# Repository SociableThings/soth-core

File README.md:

# soth-core

---

## About
Hardware core module for Sociable Things Agent.

## Architecture

Agent

Core

## Data format
### GPS
```
{
    "year": 2015,
    "month": 4,
    "day": 12,
    "hour": 14,
    "minute": 0,
    "second": 48,
    "validity": 1,
    "latitude": 35.69020,
    "longitude": 139.69001,
    "speed": 0.74,
    "heading": 102.72
}
```

## Progress

Now prototyping

## GPS bore data

valid GPRMC

```
$GPGGA,150754.000,3540.6036,N,13940.9576,E,2,5,1.85,67.2,M,39.4,M,0000,0000*6A
$GPGLL,3540.6036,N,13940.9576,E,150754.000,A,D*5D
$GPGSA,A,3,28,03,01,06,17,,,,,,,,2.08,1.85,0.95*00
$GPGSV,4,1,13,03,71,081,15,28,56,235,35,17,49,320,16,01,42,051,15*77
$GPGSV,4,2,13,11,32,077,,32,27,046,,06,20,269,35,04,17,067,*76
$GPGSV,4,3,13,23,17,136,,09,05,164,,10,05,213,,44,04,260,*74
$GPGSV,4,4,13,19,03,118,*48
$GPRMC,150754.000,A,3540.6036,N,13940.9576,E,0.06,198.48,110415,,,D*60
$GPVTG,198.48,T,,M,0.06,N,0.12,K,D*31
```

invalid GPRMC

```
$GPRMC,142307.497,V,,,,,0.00,0.00,110415,,,N*44
```

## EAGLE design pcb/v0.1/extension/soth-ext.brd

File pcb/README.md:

# soth-core PCB

---

## BOM list

| Parts # |   Parts Name   | Manufacture Parts # | Footprint | Pin | Manufacture | Source | Document |
|--------:|---------------:|--------------------:|----------:|----:|------------:|-------:|---------:|
|       U1|             MCU|      ATXMEGA32D4-AUR|       TQFP|   44|       Atmel |[Akizuki](http://akizukidenshi.com/catalog/g/gI-06993/)|[AVR XMEGA D Manual](http://www.atmel.com/ja/jp/Images/Atmel-8210-8-and-16-bit-AVR-Microcontrollers-XMEGA-D_Manual.pdf), [ATxmega32D4 Complete](http://www.atmel.com/ja/jp/Images/Atmel-8135-8-and-16-bit-AVR-microcontroller-ATxmega16D4-32D4-64D4-128D4_datasheet.pdf)|
|      IC1|USB Serial Conv.|    AE-FT231X(FT231X)|DIP(500MIL)|   18|      Akizuki|[Akizuki](http://akizukidenshi.com/catalog/g/gK-06894/)|[Manual](http://akizukidenshi.com/download/ds/akizuki/ae_ft231x_manual.pdf)|
|    IC3,4|  3-State Buffer|            TC7SZ125F|       SSOP|    5|      Toshiba|[Akizuki](http://akizukidenshi.com/catalog/g/gI-06481/)|[Datasheet](http://toshiba.semicon-storage.com/info/docget.jsp?did=20048&prodName=TC7SZ125FU)|
|      IC5| Pressure Sensor|      12113(LPS331AP)|        DIP|   10|Strawberry Linux|[Strawberry Linux](https://strawberry-linux.com/catalog/items?code=12113)|[Manual](https://strawberry-linux.com/pub/lps331ap-manual.pdf)|

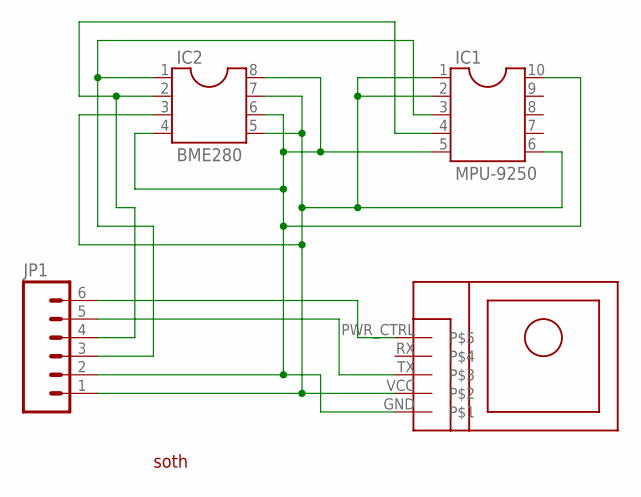
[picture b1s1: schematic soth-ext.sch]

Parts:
IC1: MPU-9250; DIL10
IC2: BME280; DIL08
JP1: M06SILK_FEMALE_PTH; 1X06
U$1: GM318B
U$2: SOTH_LOGO; SILK_LOGO

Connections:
GND: IC1.5, IC1.10, IC2.4, IC2.6, IC2.8, JP1.2, U$1.GND
unnamed: IC1.1, IC1.2, IC1.6, IC2.3, IC2.5, IC2.7, JP1.1, U$1.VCC
unnamed: JP1.5, U$1.TX
unnamed: JP1.6, U$1.PWR_CTRL
unnamed: IC1.4, IC2.2, JP1.4
unnamed: IC1.3, IC2.1, JP1.3

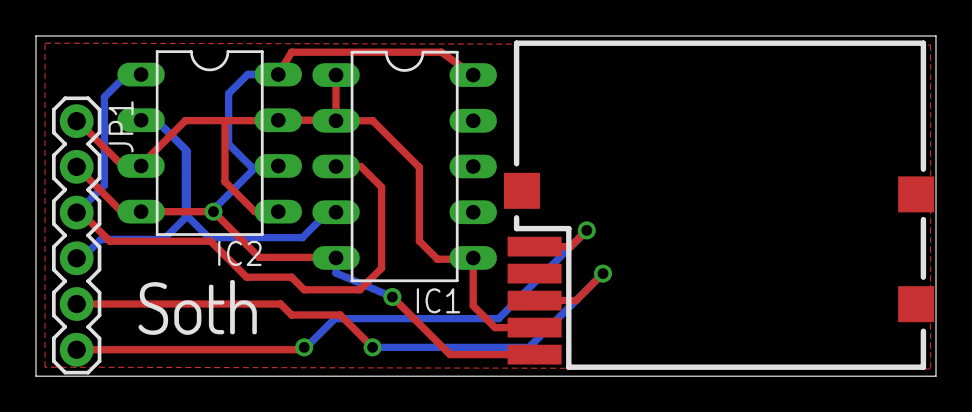
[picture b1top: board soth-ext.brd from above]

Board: 2 copper layers, 50.0 x 18.9 mm, 5 parts (0 on the bottom side), 6 nets.

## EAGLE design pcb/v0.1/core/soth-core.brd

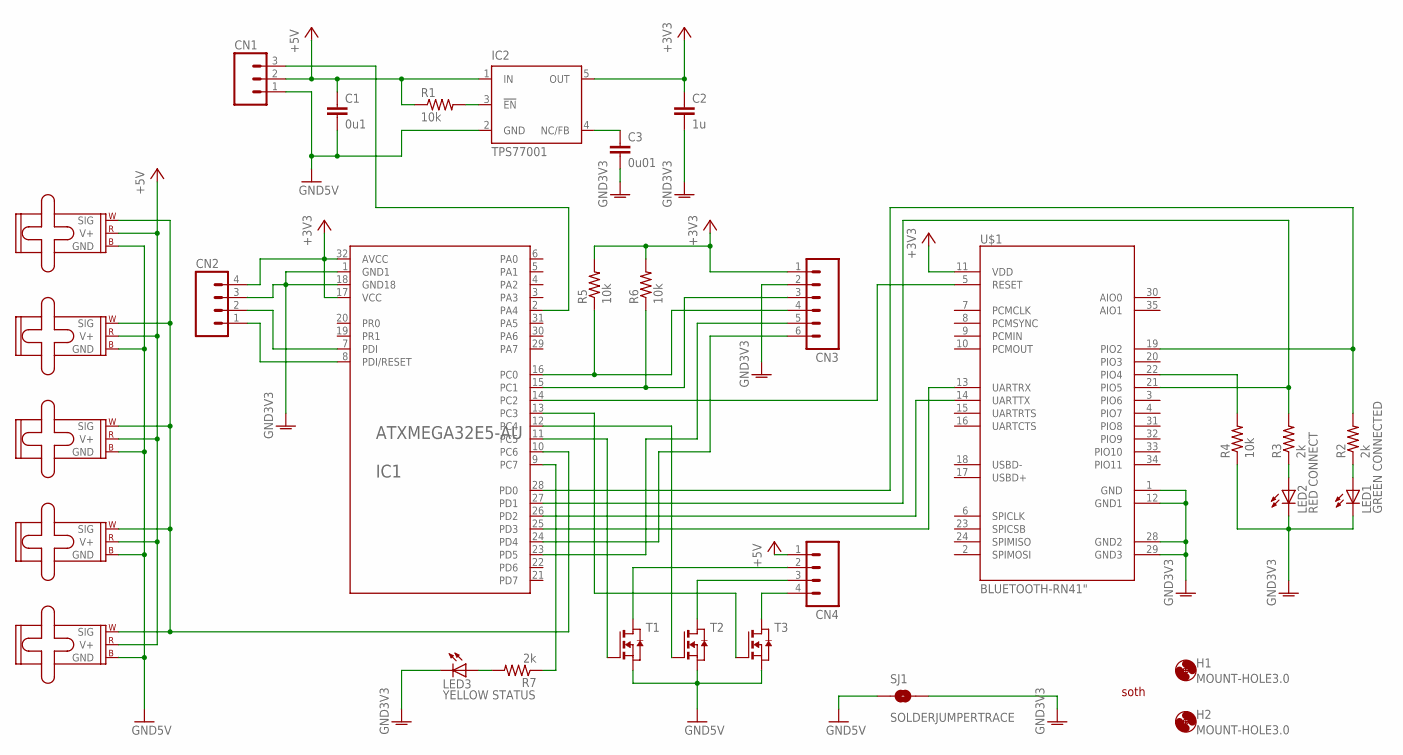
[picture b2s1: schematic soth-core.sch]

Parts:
C1: 0u1; C1608
C2: 1u; C1608
C3: 0u01; C1608
CN1: M03PTH; 1X03
CN2, CN4: M04PTH; 1X04
CN3: M06SILK_FEMALE_PTH; 1X06
H1, H2: MOUNT-HOLE3.0; 3,0
IC1: ATXMEGA32E5-AU; TQFP32-08
IC2: TPS77001; SOT23-DBV
LED1: GREEN CONNECTED; CHIPLED_1206
LED2: RED CONNECT; CHIPLED_1206
LED3: YELLOW STATUS; CHIPLED_1206
M1, M2, M3, M4, M5: SMALL_SERVO; 1X03
R1, R4, R5, R6: 10k; R0603
R2, R3, R7: 2k; R0603
SJ1: SOLDERJUMPERTRACE; SJ_2S-TRACE
T1, T2, T3: NMOSSOT23; SOT-23
U$1: BLUETOOTH-RN41"; RN41
U$2: SOTH_LOGO; SILK_LOGO

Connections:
+3V3: C2.1, CN2.4, CN3.1, IC1.17 (VCC), IC1.32 (AVCC), IC2.5 (OUT), R5.2, R6.2, U$1.11 (VDD)
+5V: C1.1, CN1.2, CN4.1, IC2.1 (IN), M1.2 (V+), M2.2 (V+), M3.2 (V+), M4.2 (V+), M5.2 (V+), R1.1
GND: C1.2, CN1.1, IC2.2 (GND), M1.3 (GND), M2.3 (GND), M3.3 (GND), M4.3 (GND), M5.3 (GND), SJ1.1, T1.2 (S), T2.2 (S), T3.2 (S)
GNDA: C2.2, C3.2, CN2.3, CN3.2, IC1.1 (GND1), IC1.18 (GND18), LED1.C, LED2.C, LED3.C, R4.1, SJ1.2, U$1.1 (GND), U$1.12 (GND1), U$1.28 (GND2), U$1.29 (GND3)
unnamed: CN4.2, T1.1 (D)
unnamed: IC2.3 (!EN), R1.2
unnamed: IC1.26 (PD2), U$1.14 (UARTTX)
unnamed: CN2.2, IC1.7 (PDI)
unnamed: CN2.1, IC1.8 (PDI/RESET)
unnamed: IC1.25 (PD3), U$1.13 (UARTRX)
unnamed: IC1.27 (PD1), R3.2, U$1.21 (PIO5)
unnamed: LED2.A, R3.1
unnamed: LED1.A, R2.1
unnamed: IC1.28 (PD0), R2.2, U$1.19 (PIO2)
unnamed: R4.2, U$1.22 (PIO4)
unnamed: CN3.4, IC1.16 (PC0), R5.1
unnamed: CN3.3, IC1.15 (PC1), R6.1
unnamed: CN1.3, IC1.2 (PA4)
unnamed: CN4.3, T2.1 (D)
unnamed: CN4.4, T3.1 (D)
unnamed: IC1.9 (PC7), R7.1
unnamed: IC1.11 (PC5), T1.3 (G)
unnamed: CN3.6, IC1.24 (PD4)
unnamed: IC1.10 (PC6), M1.1 (SIG), M2.1 (SIG), M3.1 (SIG), M4.1 (SIG), M5.1 (SIG)
unnamed: CN3.5, IC1.23 (PD5)
unnamed: IC1.12 (PC4), T2.3 (G)
unnamed: IC1.13 (PC3), T3.3 (G)
unnamed: LED3.A, R7.2
unnamed: C3.1, IC2.4 (NC/FB)
unnamed: IC1.14 (PC2), U$1.5 (RESET)

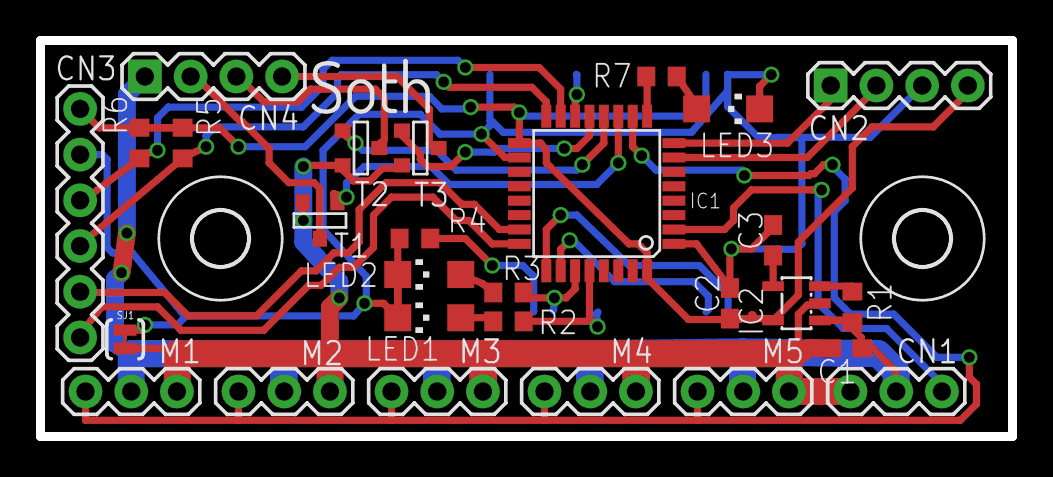
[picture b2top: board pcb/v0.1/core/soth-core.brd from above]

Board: 2 copper layers, 54.0 x 22.0 mm, 32 parts (1 on the bottom side), 30 nets.

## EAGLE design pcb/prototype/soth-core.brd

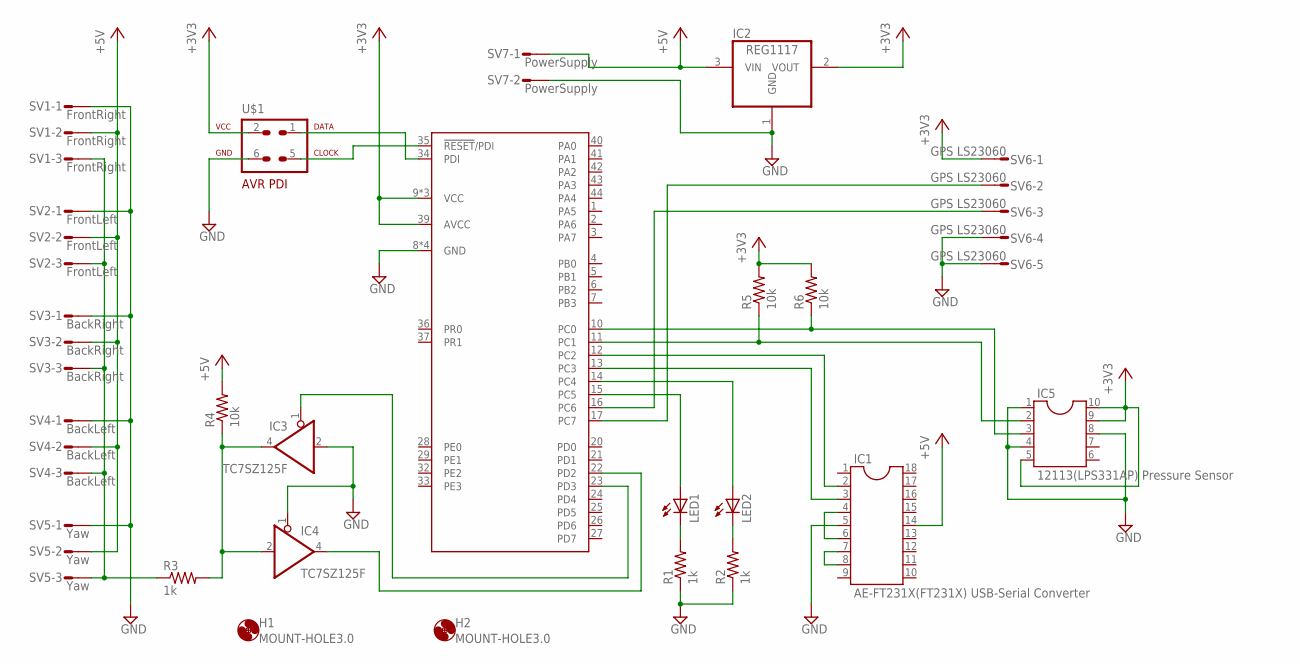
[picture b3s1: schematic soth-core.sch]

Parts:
H1, H2: MOUNT-HOLE3.0; 3,0
IC1: AE-FT231X(FT231X) USB-Serial Converter; SOCKET-18
IC2: REG1117; SOT223
IC3, IC4: TC7SZ125F; SOT23-5
IC5: 12113(LPS331AP) Pressure Sensor; DIL10
LED1, LED2: LED; SMARTLED-TTW
R1, R2, R3: 1k; R0805
R4, R5, R6: 10k; R0805
SV1: FrontRight; S03P
SV2: FrontLeft; S03P
SV3: BackRight; S03P
SV4: BackLeft; S03P
SV5: Yaw; S03P
SV6: GPS LS23060; S05P
SV7: PowerSupply; S02P
U1: ATXMEGA32D4-AU; TQFP-44A-44
U$1: AVR-PDIVERT; AVR-ISP-6

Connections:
+3V3: IC2.2 (VOUT), IC5.5, IC5.9, IC5.10, R5.2, R6.2, SV6.1, U1.9 (VCC), U1.19 (VCC), U1.31 (VCC), U1.39 (AVCC), U$1.2
+5V: IC1.14, IC2.3 (VIN), R4.2, SV1.2, SV2.2, SV3.2, SV4.2, SV5.2, SV7.1
GND: IC1.5, IC2.1 (GND), IC3.2 (I), IC3.3 (GND), IC4.1 (OE), IC4.3 (GND), IC5.1, IC5.4, IC5.8, R1.1, R2.1, SV1.1, SV2.1, SV3.1, SV4.1, SV5.1, SV6.4, SV6.5, SV7.2, U1.8 (GND), U1.18 (GND), U1.30 (GND), U1.38 (GND), U$1.6
unnamed: R3.1, SV1.3, SV2.3, SV3.3, SV4.3, SV5.3
unnamed: LED1.A@1 (A), U1.15 (PC5)
unnamed: LED2.A@1 (A), U1.14 (PC4)
unnamed: LED1.C@1 (C), R1.2
unnamed: U1.35 (!RESET!/PDI), U$1.5
unnamed: U1.34 (PDI), U$1.1
unnamed: LED2.C@1 (C), R2.2
unnamed: IC4.4 (O), U1.22 (PD2)
unnamed: SV6.2, U1.17 (PC7)
unnamed: IC1.2, U1.12 (PC2)
unnamed: IC1.3, U1.13 (PC3)
unnamed: IC1.7, IC1.8
unnamed: IC1.4, IC1.6
unnamed: SV6.3, U1.16 (PC6)
unnamed: IC3.1 (OE), U1.23 (PD3)
unnamed: IC3.4 (O), IC4.2 (I), R3.2, R4.1
unnamed: IC5.3, R6.1, U1.10 (PC0)
unnamed: IC5.2, R5.1, U1.11 (PC1)
VCC: IC3.5 (VCC), IC4.5 (VCC)

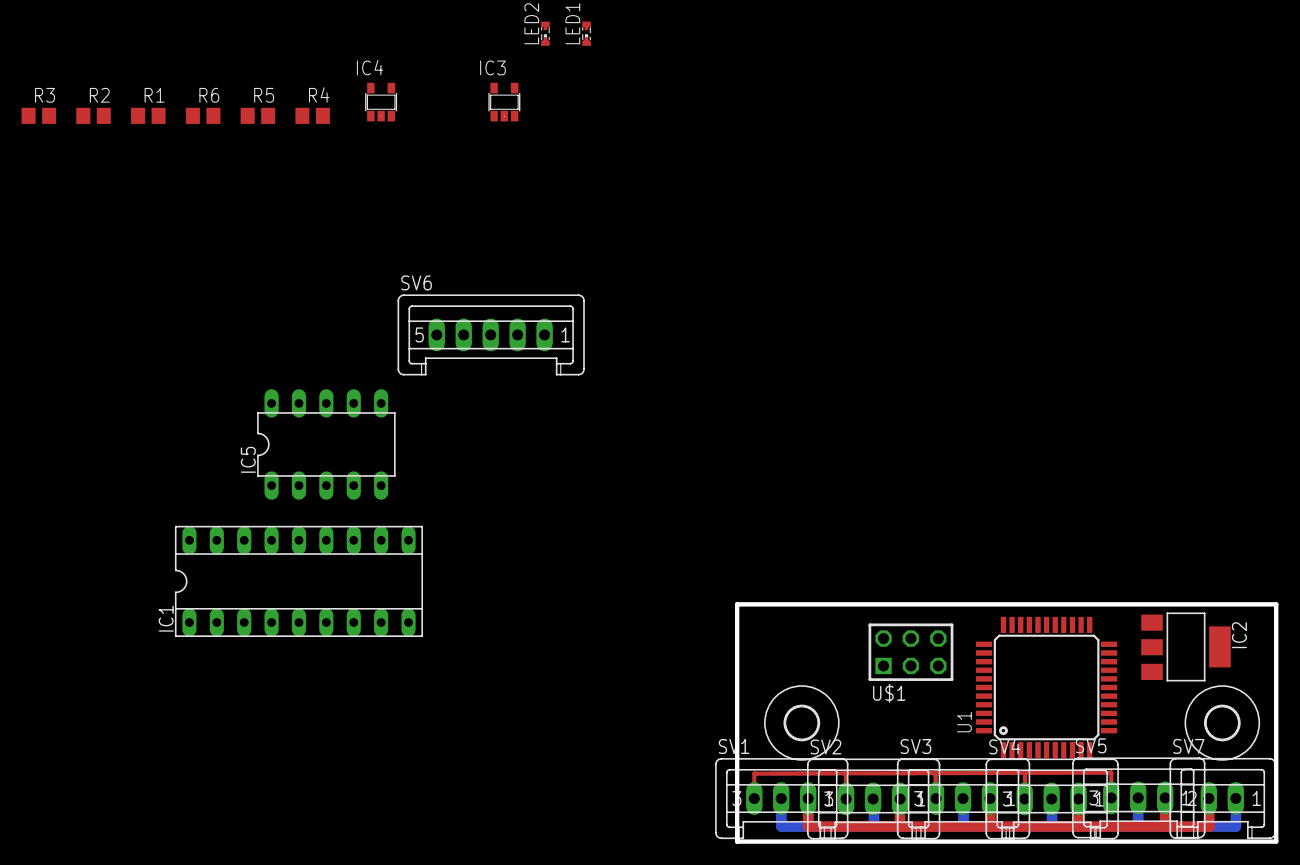
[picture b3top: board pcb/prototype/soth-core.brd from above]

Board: 2 copper layers, 50.0 x 22.0 mm, 24 parts (0 on the bottom side), 22 nets.

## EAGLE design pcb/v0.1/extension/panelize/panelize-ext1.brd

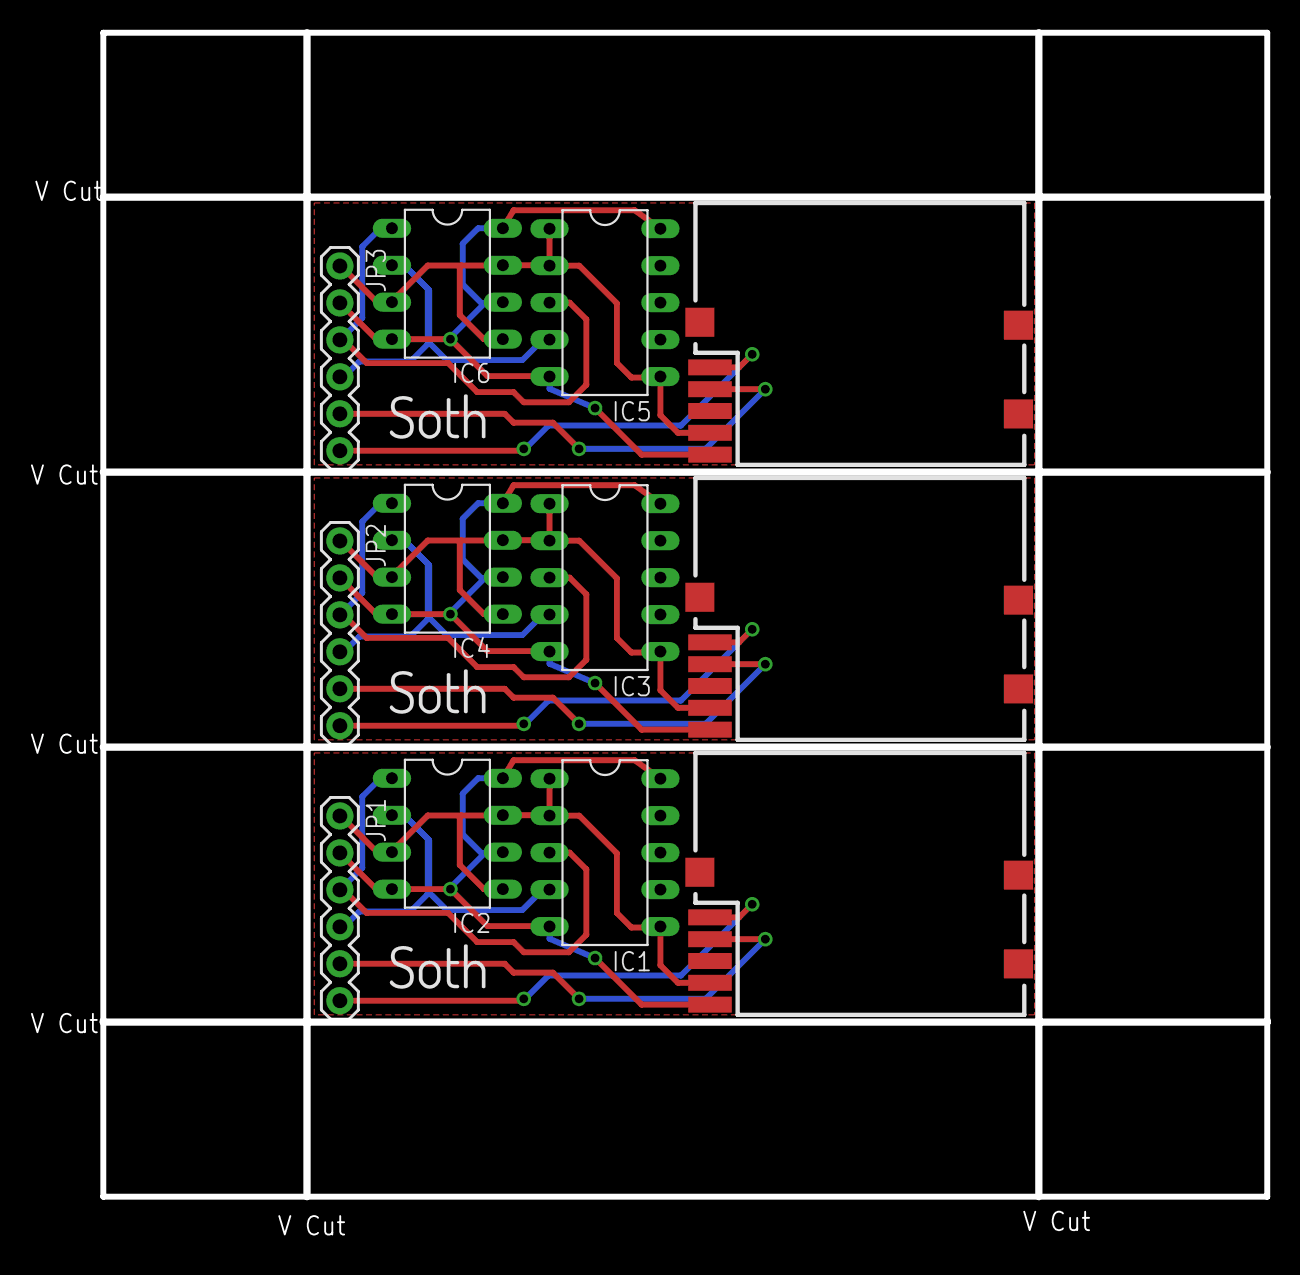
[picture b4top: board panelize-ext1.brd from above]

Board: 2 copper layers, 80.0 x 80.0 mm, 15 parts (0 on the bottom side), 18 nets.

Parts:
IC1, IC3, IC5: MPU-9250; DIL10
IC2, IC4, IC6: BME280; DIL08
JP1, JP2, JP3: 1X06
U$1, U$3, U$5: GM318B
U$2, U$4, U$6: SOTH_LOGO; SILK_LOGO

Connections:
GND: IC1.5, IC1.10, IC2.4, IC2.6, IC2.8, JP1.2, U$1.GND
GND1: IC3.5, IC3.10, IC4.4, IC4.6, IC4.8, JP2.2, U$3.GND
GND2: IC5.5, IC5.10, IC6.4, IC6.6, IC6.8, JP3.2, U$5.GND
unnamed: JP2.5, U$3.RX
unnamed: IC1.1, IC1.2, IC1.6, IC2.3, IC2.5, IC2.7, JP1.1, U$1.VCC
unnamed: JP1.5, U$1.RX
unnamed: JP1.6, U$1.PWR_CTRL
unnamed: JP2.6, U$3.PWR_CTRL
unnamed: IC3.4, IC4.2, JP2.4
unnamed: IC1.4, IC2.2, JP1.4
unnamed: IC1.3, IC2.1, JP1.3
unnamed: IC3.3, IC4.1, JP2.3
unnamed: IC3.1, IC3.2, IC3.6, IC4.3, IC4.5, IC4.7, JP2.1, U$3.VCC
unnamed: JP3.5, U$5.RX
unnamed: JP3.6, U$5.PWR_CTRL
unnamed: IC5.4, IC6.2, JP3.4
unnamed: IC5.3, IC6.1, JP3.3
unnamed: IC5.1, IC5.2, IC5.6, IC6.3, IC6.5, IC6.7, JP3.1, U$5.VCC

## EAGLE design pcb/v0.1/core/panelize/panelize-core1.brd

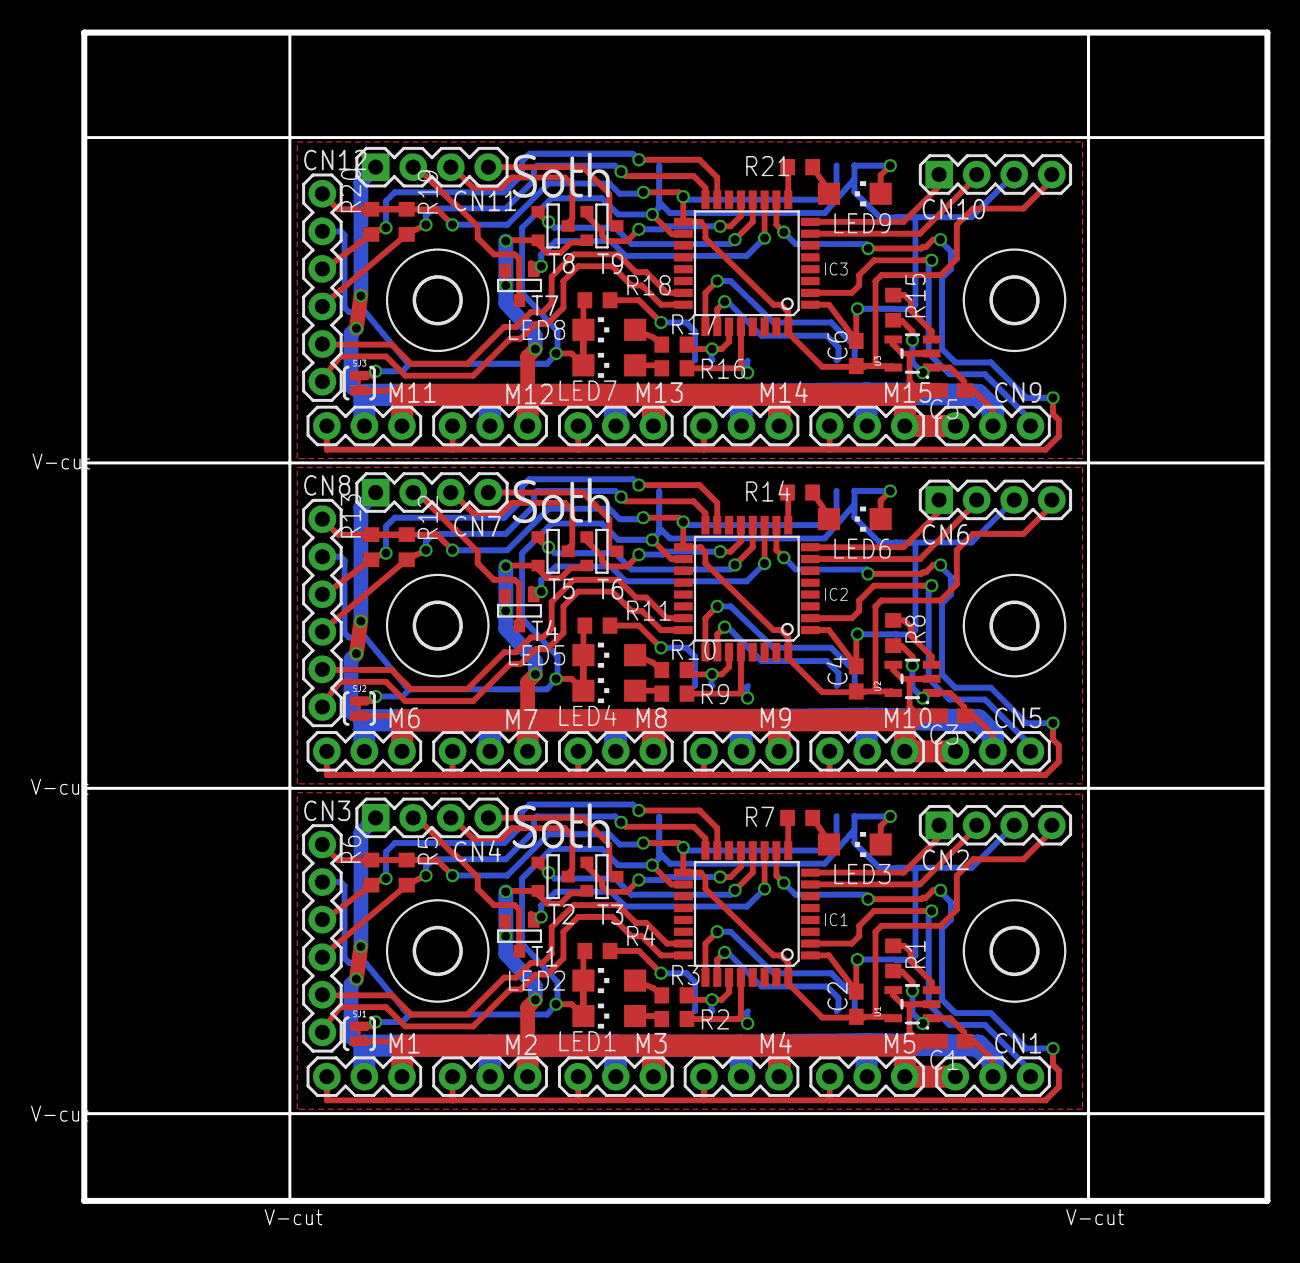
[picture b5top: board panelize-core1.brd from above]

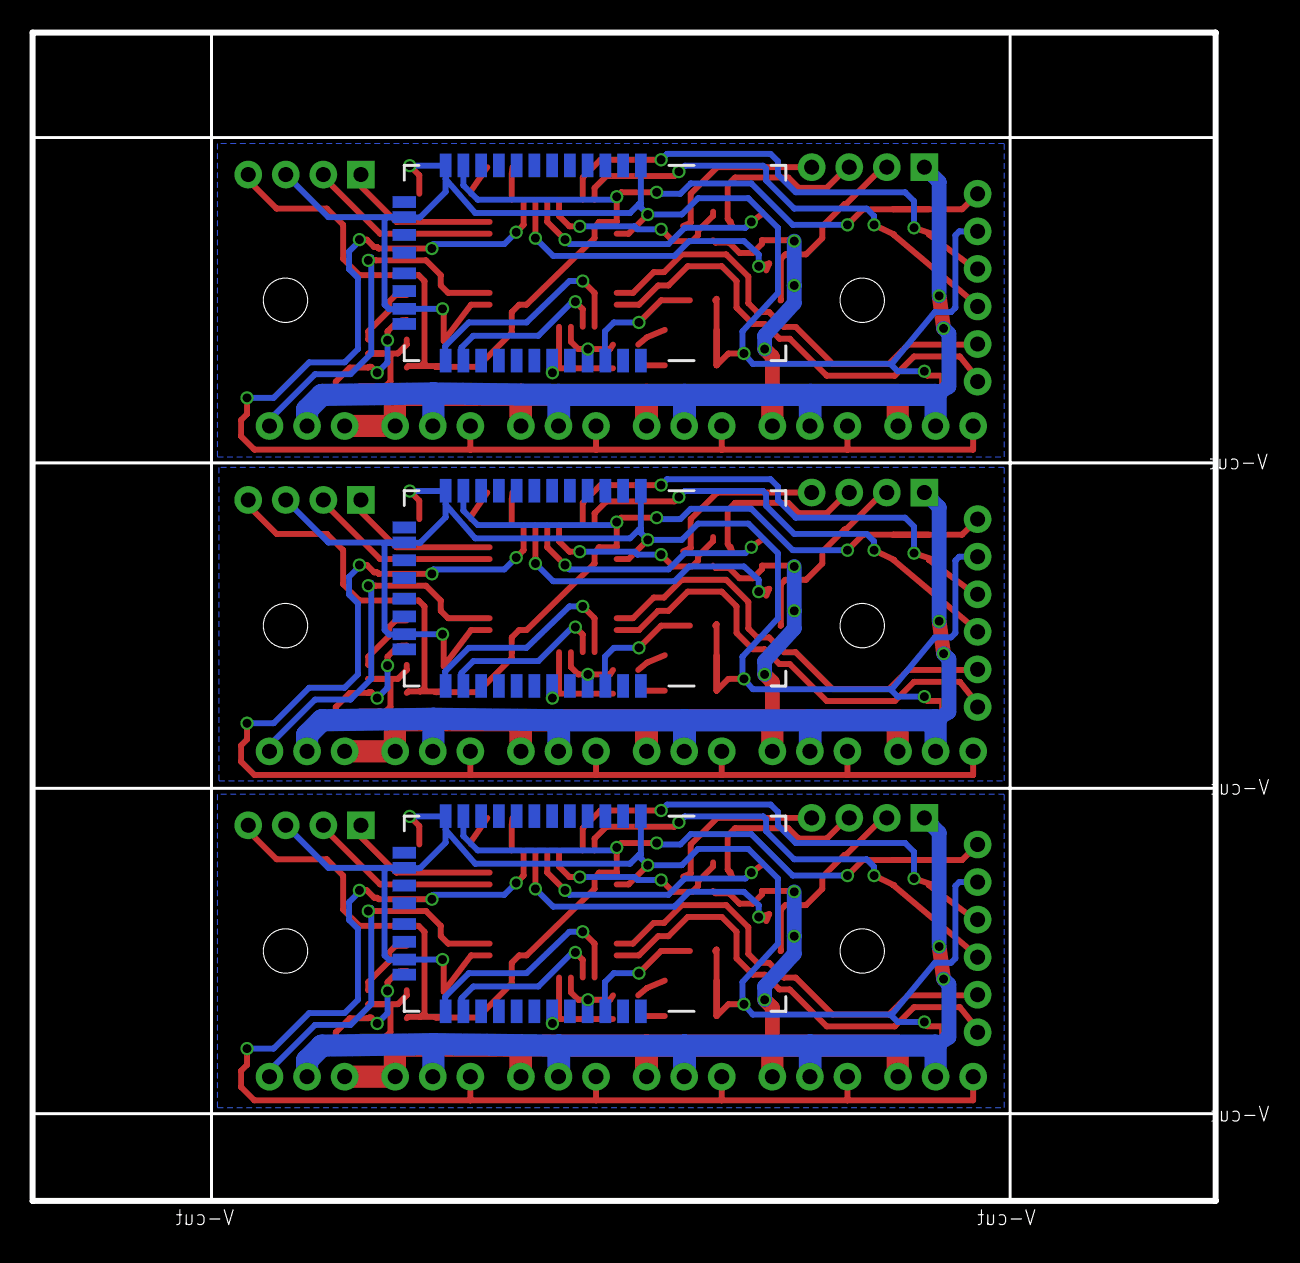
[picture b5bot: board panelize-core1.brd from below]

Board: 2 copper layers, 80.0 x 79.0 mm, 93 parts (3 on the bottom side), 84 nets.

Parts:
C1, C3, C5: 0u1; C1608
C2, C4, C6: 1u; C1608
CN1, CN5, CN9: 1X03
CN2, CN4, CN6, CN7, CN10, CN11: 1X04
CN3, CN8, CN12: 1X06
H1, H2, H3, H4, H5, H6: MOUNT-HOLE3.0; 3,0
IC1, IC2, IC3: ATXMEGA32E5-AU; TQFP32-08
LED1, LED4, LED7: RED CONNECT; CHIPLED_1206
LED2, LED5, LED8: GREEN CONNECTED; CHIPLED_1206
LED3, LED6, LED9: GREEN STATUS; CHIPLED_1206
M1, M2, M3, M4, M5, M6, M7, M8, M9, M10, M11, M12, M13, M14, M15: SMALL_SERVO; 1X03
R1, R4, R5, R6, R8, R11, R12, R13, R15, R18, R19, R20: 10k; R0603
R2, R3, R7, R9, R10, R14, R16, R17, R21: 1k; R0603
SJ1, SJ2, SJ3: SOLDERJUMPERTRACE; SJ_2S-TRACE
T1, T2, T3, T4, T5, T6, T7, T8, T9: SOT-23
U1, U2, U3: LDO-TPS78233; SOT23-5
U$1, U$3, U$5: BLUETOOTH-RN41"; RN41
U$2, U$4, U$6: SOTH_LOGO; SILK_LOGO

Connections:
+3V1: C4.1, CN6.4, CN8.1, IC2.17, IC2.32, R12.2, R13.2, U2.5, U$3.11
+3V2: C6.1, CN10.4, CN12.1, IC3.17, IC3.32, R19.2, R20.2, U3.5, U$5.11
+3V3: C2.1, CN2.4, CN3.1, IC1.17, IC1.32, R5.2, R6.2, U1.5, U$1.11
+5V: C1.1, CN1.2, CN4.1, M1.2, M2.2, M3.2, M4.2, M5.2, R1.1, U1.1
+5V1: C3.1, CN5.2, CN7.1, M6.2, M7.2, M8.2, M9.2, M10.2, R8.1, U2.1
+5V2: C5.1, CN9.2, CN11.1, M11.2, M12.2, M13.2, M14.2, M15.2, R15.1, U3.1
GND: C1.2, CN1.1, M1.3, M2.3, M3.3, M4.3, M5.3, SJ1.1, T1.2, T2.2, T3.2, U1.2, U1.4
GND1: C3.2, CN5.1, M6.3, M7.3, M8.3, M9.3, M10.3, SJ2.1, T4.2, T5.2, T6.2, U2.2, U2.4
GND2: C5.2, CN9.1, M11.3, M12.3, M13.3, M14.3, M15.3, SJ3.1, T7.2, T8.2, T9.2, U3.2, U3.4
GNDA: C2.2, CN2.3, CN3.2, IC1.1, IC1.18, LED1.C, LED2.C, LED3.C, R4.1, SJ1.2, U$1.1, U$1.12, U$1.28, U$1.29
GNDA1: C4.2, CN6.3, CN8.2, IC2.1, IC2.18, LED4.C, LED5.C, LED6.C, R11.1, SJ2.2, U$3.1, U$3.12, U$3.28, U$3.29
GNDA2: C6.2, CN10.3, CN12.2, IC3.1, IC3.18, LED7.C, LED8.C, LED9.C, R18.1, SJ3.2, U$5.1, U$5.12, U$5.28, U$5.29
unnamed: CN4.2, T1.1
unnamed: R1.2, U1.3
unnamed: IC1.26, U$1.14
unnamed: CN2.2, IC1.7
unnamed: CN2.1, IC1.8
unnamed: IC1.25, U$1.13
unnamed: IC1.27, R3.2, U$1.21
unnamed: LED2.A, R3.1
unnamed: LED1.A, R2.1
unnamed: IC1.28, R2.2, U$1.19
unnamed: R4.2, U$1.22
unnamed: CN3.4, IC1.16, R5.1
unnamed: CN3.3, IC1.15, R6.1
unnamed: CN1.3, IC1.2
unnamed: CN4.3, T2.1
unnamed: CN4.4, T3.1
unnamed: IC1.9, R7.1
unnamed: IC1.11, T1.3
unnamed: CN3.6, IC1.24
unnamed: IC1.10, M1.1, M2.1, M3.1, M4.1, M5.1
unnamed: CN3.5, IC1.23
unnamed: IC1.12, T2.3
unnamed: IC1.13, T3.3
unnamed: LED3.A, R7.2
unnamed: R8.2, U2.3
unnamed: CN6.2, IC2.7
unnamed: CN6.1, IC2.8
unnamed: IC2.26, U$3.14
unnamed: IC2.25, U$3.13
unnamed: IC2.27, R10.2, U$3.21
unnamed: LED5.A, R10.1
unnamed: LED4.A, R9.1
unnamed: IC2.28, R9.2, U$3.19
unnamed: R11.2, U$3.22
unnamed: CN8.4, IC2.16, R12.1
unnamed: CN8.3, IC2.15, R13.1
unnamed: CN5.3, IC2.2
unnamed: IC2.10, M6.1, M7.1, M8.1, M9.1, M10.1
unnamed: CN8.6, IC2.24
unnamed: CN8.5, IC2.23
unnamed: CN7.2, T4.1
unnamed: CN7.3, T5.1
unnamed: CN7.4, T6.1
unnamed: IC2.11, T4.3
unnamed: IC2.12, T5.3
unnamed: IC2.13, T6.3
unnamed: IC2.9, R14.1
unnamed: LED6.A, R14.2
unnamed: R15.2, U3.3
unnamed: CN10.2, IC3.7
unnamed: CN10.1, IC3.8
unnamed: IC3.26, U$5.14
unnamed: IC3.25, U$5.13
unnamed: IC3.27, R17.2, U$5.21
unnamed: LED8.A, R17.1
unnamed: LED7.A, R16.1
unnamed: IC3.28, R16.2, U$5.19
unnamed: R18.2, U$5.22
unnamed: CN12.4, IC3.16, R19.1
unnamed: CN12.3, IC3.15, R20.1
unnamed: CN9.3, IC3.2
unnamed: IC3.10, M11.1, M12.1, M13.1, M14.1, M15.1
unnamed: CN12.6, IC3.24
unnamed: CN12.5, IC3.23
unnamed: CN11.2, T7.1
unnamed: CN11.3, T8.1
unnamed: CN11.4, T9.1
unnamed: IC3.11, T7.3
unnamed: IC3.12, T8.3
unnamed: IC3.13, T9.3
unnamed: IC3.9, R21.1
unnamed: LED9.A, R21.2

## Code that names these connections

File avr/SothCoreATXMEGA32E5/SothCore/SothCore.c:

/*
 * SothCore.c
 *
 * Author: Hideyuki Takei <hide@soth.io>
 */

#include <avr/io.h>
#include <util/delay.h>
#include <avr/pgmspace.h>
#include <avr/interrupt.h>  
#include <stdlib.h>
#include "SothCore.h"
#include "UsartCommunication.h"
#include "UsartGPS.h"
#include "I2C.h"
#include "BME280.h"
#include "UsartCmdServo.h"
#include "xprintf.h"
#include "MotionControl.h"
#include "MPU9150.h"

#define WAIT_TIME 200
#define UP_ANGLE 900
#define DOWN_ANGLE 700
#define CLOSE_ANGLE 0
#define RIGHT_YAW 200
#define LEFT_YAW -200
#define CENTER_YAW -30

// Prototypes
void initClock();
void initPort();
void onReadSensor(float temperature, float pressure, float humidity);
void onReadAccSensor(int16_t accX, double accY, double accZ);

int main(void)
{	
	char jsonString[1000];
    uint8_t servoData[200];

    // Initialization
	initPort();
	initClock();
	initUsartComm();
	initUsartGPS();
    initI2C();
	initUsartCmdServo();
    initBME280();
    initMPU9150();

    // Enable interrupt
    PMIC_CTRL =  PMIC_LOLVLEN_bm | PMIC_MEDLVLEN_bm | PMIC_HILVLEN_bm;  // enable high/middle level interrupt executing
    sei();

    _delay_ms(1000);

    /*while(1){
        readAccGyro(onReadAccSensor);
        _delay_ms(2000);
    }*/

    //setStandaloneMotion();
    setOldStandaloneMotion();

    // LED test
    /*
    while(1){
        offLedStatus();
        _delay_ms(1000);
        onLedStatus();
        _delay_ms(1000);
        xprintf("hogege\r\n");
        //_delay_ms(1000);
        //xprintf("R,1\r\n");
    }
    */
    
    /*// GPS test
    powerOnGPS();
    while(1)
    {
		onLedStatus();
		_delay_ms(100);
		offLedStatus();
		_delay_ms(100);
        
        getGPRMCInfoAsJson(jsonString);
        //sendStringToComm(jsonString);

        _delay_ms(1000);
    }*/
    
    /*// I2C test
    uint8_t data[] = {0x20, 0x90};
    addQueue(0b10111000, 2, data, 0, testI2C);

    _delay_ms(2000);
    
    uint8_t data2[] = {0x28};
    addQueue(0b10111000, 1, data2, 1, testI2C);

    uint8_t data3[] = {0x29};
    addQueue(0b10111000, 1, data3, 1, testI2C);

    uint8_t data4[] = {0x2A};
    addQueue(0b10111000, 1, data4, 1, testI2C);*/

    
    /*// Temperature, pressure, humidity
    _delay_ms(1000);

    initBME280();

    while(1){
        //uint8_t address[] = {0xD0};
        //addQueue(0b11101100, 1, address, 1, testI2C);
        //address[0] = 0x75;
        //addQueue(0b11010000, 1, address, 1, testI2C);
        readTemperaturePressureHumidity(onReadSensor);

        _delay_ms(5000);

        onLedStatus();
        _delay_ms(100);
        offLedStatus();
        _delay_ms(100);
    }*/
    

    /*// Proto3 test
    uint8_t buffer[128];
    size_t message_length;
    bool status;

    RobotInfoRequest request;
    pb_ostream_t stream = pb_ostream_from_buffer(buffer, sizeof(buffer));
    request.robot_id = 10;

    status = pb_encode(&stream, RobotInfoRequest_fields, &request);
    message_length = stream.bytes_written;

    if (!status)
    {
        xprintf("Encoding failed: %s\n", PB_GET_ERROR(&stream));
        return 1;
    }

    RobotInfoRequest req2;
    pb_istream_t stream2 = pb_istream_from_buffer(buffer, message_length);
    status = pb_decode(&stream2, RobotInfoRequest_fields, &req2);

    if (!status)
    {
        xprintf("Decoding failed: %s\n", PB_GET_ERROR(&stream2));
        return 1;
    }

    onLedStatus();
    while(1){
        uint16_t length = recvCharacters(servoData, 3);
        if(length>0){
            break;
        }
    }
    _delay_ms(1000);

    while(1){
        onLedStatus();
        _delay_ms(500);
        offLedStatus();
        _delay_ms(500);
        xprintf("Your lucky number was %d!\n", req2.robot_id);
    }*/

    /*
    // pb test
    _delay_ms(500);
    
    changeTorqueOnForAllServos();

    while(1){
        //onLedStatus();
        _delay_ms(500);
        //offLedStatus();
    }*/
}

void onReadAccSensor(int16_t accX, double accY, double accZ)
{

}

void onReadSensor(float temperature, float pressure, float humidity)
{
    char temperatureString[20], pressureString[20], humidityString[20];
    
    xprintf("## Recv sensor\n");
    
    dtostrf(temperature, 2, 2, temperatureString);
    dtostrf(pressure, 2, 2, pressureString);
    dtostrf(humidity, 2, 2, humidityString);
    xprintf("Temperature: %sdeg, Pressure: %shPa, Humidity: %s%%\n", temperatureString, pressureString, humidityString);
}

void initClock()
{
	// Set int. 2MHz Clock
	OSC.CTRL = OSC_RC2MEN_bm;
	loop_until_bit_is_set(OSC.STATUS, OSC_RC2MRDY_bp);

	// Set clock selector: Int. 2MHz
	CPU_CCP = CCP_IOREG_gc;
	CLK.CTRL = CLK_SCLKSEL_RC2M_gc;
	
	// Set Pre-scaler DIV2 (Sys CLK: 1MHz)
	CPU_CCP = CCP_IOREG_gc;
	CLK.PSCTRL = CLK_PSADIV_2_gc;
}

void initPort()
{    
    // PORTA:     11101111
    //            |||||||+- PA0( 6): NC
    //            ||||||+-- PA1( 5): NC
    //            |||||+--- PA2( 4): NC
    //            ||||+---- PA3( 3): NC
    //            |||+----- PA4( 2): Power voltage ADC
    //            ||+------ PA5(31): NC
    //            |+------- PA6(30): NC
    //            +-------- PA7(29): NC
    PORTA_DIR = 0b11101111;
    PORTA_OUT = 0b11101111;

    // PORTC:     11111110
    //            |||||||+- PC0(16): SDA I2C for sensors
    //            ||||||+-- PC1(15): SCL I2C for sensors
    //            |||||+--- PC2(14): Bluetooth /RESET (Active low)
    //            ||||+---- PC3(13): Eye LED(Red)
    //            |||+----- PC4(12): Eye LED(Green)
    //            ||+------ PC5(11): Eye LED(Blue)
    //            |+------- PC6(10): RXC0 Command Servo (One wire half duplex)
    //            +-------- PC7( 9): Status LED(Yellow)
	PORTC_DIR = 0b11111110;
	PORTC_OUT = 0b11111110;
    PORTC_REMAP = 0b00010000; // Remap USARTC0 from PC0-3 to PC4-7
	
    // PORTD:     11011000
    //            |||||||+- PD0(28): Port of Bluetooth Connected LED(Red)
    //            ||||||+-- PD1(27): Port of Bluetooth Connect LED(Green)
    //            |||||+--- PD2(26): RXD0 Bluetooth SPP
    //            ||||+---- PD3(25): TXD0 Bluetooth SPP
    //            |||+----- PD4(24): Power Control of GPS (Active low)
    //            ||+------ PD5(23): Software UART RX for GPS
    //            |+------- PD6(22): NC
    //            +-------- PD7(21): NC
    PORTD_DIR = 0b11011000;
	PORTD_OUT = 0b11001000;

	offLedStatus();
    powerOffGPS();

    // Virtual Port
    // VPORT0: Virtual Port A
    // VPORT1: Virtual Port C
    // VPORT2: Virtual Port D
    // VPORT3: Virtual Port R
}

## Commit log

2015-04-04 Add avr project.
2015-04-04 add clock setting function.
2015-04-05 add usart initilization func.
2015-04-05 Add readme
2015-04-11 add nodejs proj for visualiser
2015-04-11 add suart library and atxmega library for pcb.
2015-04-12 add VPORT settings. Software UART works fine.
2015-04-12 add xprintf files. Output JSON for GPS
2015-04-12 add GPS json data format.
2015-04-12 add gps visualiser
2015-04-14 add gps bore data on readme.
2015-04-14 add soth theme.
2015-04-15 add connection widget.
2015-04-18 implemented Soth-Communicator settings
2015-04-18 update progress on readme
2015-04-19 change img format from png to jpg
2015-05-22 add pcb data.
2015-05-22 add current circuit schematic
2015-05-23 add schematic image.
2015-05-29 change pullup voltage of 3 state buffers from 3V3 to 5V0
2015-05-29 Add Command Servo functions.
2015-05-30 Add command servo recv functions.
2015-05-30 woops... GPS baudrate and update rate was reseted.
2015-05-30 implemented changing servo id function.
2015-05-30 apply unique servo id.
2015-05-30 add long packet functions.
2015-06-06 add i2c code
2015-06-06 add queue for I2C
2015-06-07 I2C multi bytes sending doesn't work
2015-06-08 works fine.
2015-06-08 Motion check.
2015-06-15 Created v0.1
2015-06-16 add beta-Gnd and ext board.
2015-06-16 add sent pcb files to Elecrow
2015-06-20 walk test
2015-06-28 Bugfix pcb design. Replace LDO parts.
2015-06-29 remove current avr project.
2015-07-04 Change microcontroller from atxmega32d4 to atxmega32e5
2015-07-04 succcessfully tx/rx data from command servos
2015-07-04 Successfully gps data rcv.
2015-07-05 Add BME280 code.
2015-07-05 Bugfix BME280 sensors handling
2015-07-05 add files of 9Axis sensor MPU-9150
2015-07-25 Add MBE280 files.
2015-07-31 Add gateway proto
2015-08-01 Add Transition easing
2015-08-01 add new easing motion.
2015-08-01 update motion.
2015-08-03 add MPU9150 process.

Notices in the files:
parts and their libraries:
SparkFun-RF: Licensing: Creative Commons ShareAlike 4.0 International - https://creativecommons.org/licenses/by-sa/4.0
